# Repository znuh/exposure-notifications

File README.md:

# Exposure Notifications
Printed Circuit Boards for the Covid-19 Exposure Notifications Visualizer - 
[see this for more details](https://znu.nz/exposure_notifications-en)

To remake Exposure Notifications you need to get/make four things:
- a BBC micro:bit or Calliope Mini with the [microbit-corona-scanner](https://github.com/znuh/microbit-corona-scanner) installed
- a black 23x23cm RIBBA frame from IKEA
- the printed circuit board for the LEDs - see the leds/ directory of this repository
- the printed circuit board for the LED matrix controller - **either** matrixctl-v1 **OR** matrixctl-v2
  - matrixctl-v2 includes a socket for the micro:bit and a switching voltage regulator
  - matrixctl-v1 comes without a socket for the micro:bit and has no switching voltage regulator
  - v2 is more efficient and keeps the LED matrix driver cooler when more LEDs light up - therefore I recommend using v2

The printed circuit board designs are made with a **Nightly Development Build** of [KiCAD](https://kicad-pcb.org/).
If you want to open/edit them you also need a recent Nightly Development Build. If you just want to use the PCBs unmodified you can also use the gerber-files from the gerber-subdirectories.

## LED matrix board
The LED matrix board uses Würth 150141RV73100 LEDs. These are bicolor-LEDs but only the red LED is used.
The landing pads for the LEDs have been reduced to a minimum to hide the pads underneath the LEDs. All PCB tracks are on the back side of the PCB. 1206 0-Ohms resistors are used instead of vias to cross tracks.

## matrixctl v2 board ##
The part number of the micro:bit socket is PIS-1240. The Micro-USB connector is a Molex 105017-0001. You can get these parts and all additional components from digi-key.

Following a recommendation from the IS31FL3738 datasheet the board includes a Tantalum Capacitor to avoid audible noise produced by ceramics capacitors through the [piezoelectric effect](https://product.tdk.com/en/contact/faq/31_singing_capacitors_piezoelectric_effect.pdf). Tantalum is a conflict resource. I've chosen a Kemet T495B336K010ATE450 because Kemet is a sane choice in general and their handling of the issue sounds ok.

If you do not want to use the micro:bit socket you can also connect the micro:bit or a Calliope Mini to the pin header of the PCB. You need to connect I²C (SCL and SDA), 3V and GND.

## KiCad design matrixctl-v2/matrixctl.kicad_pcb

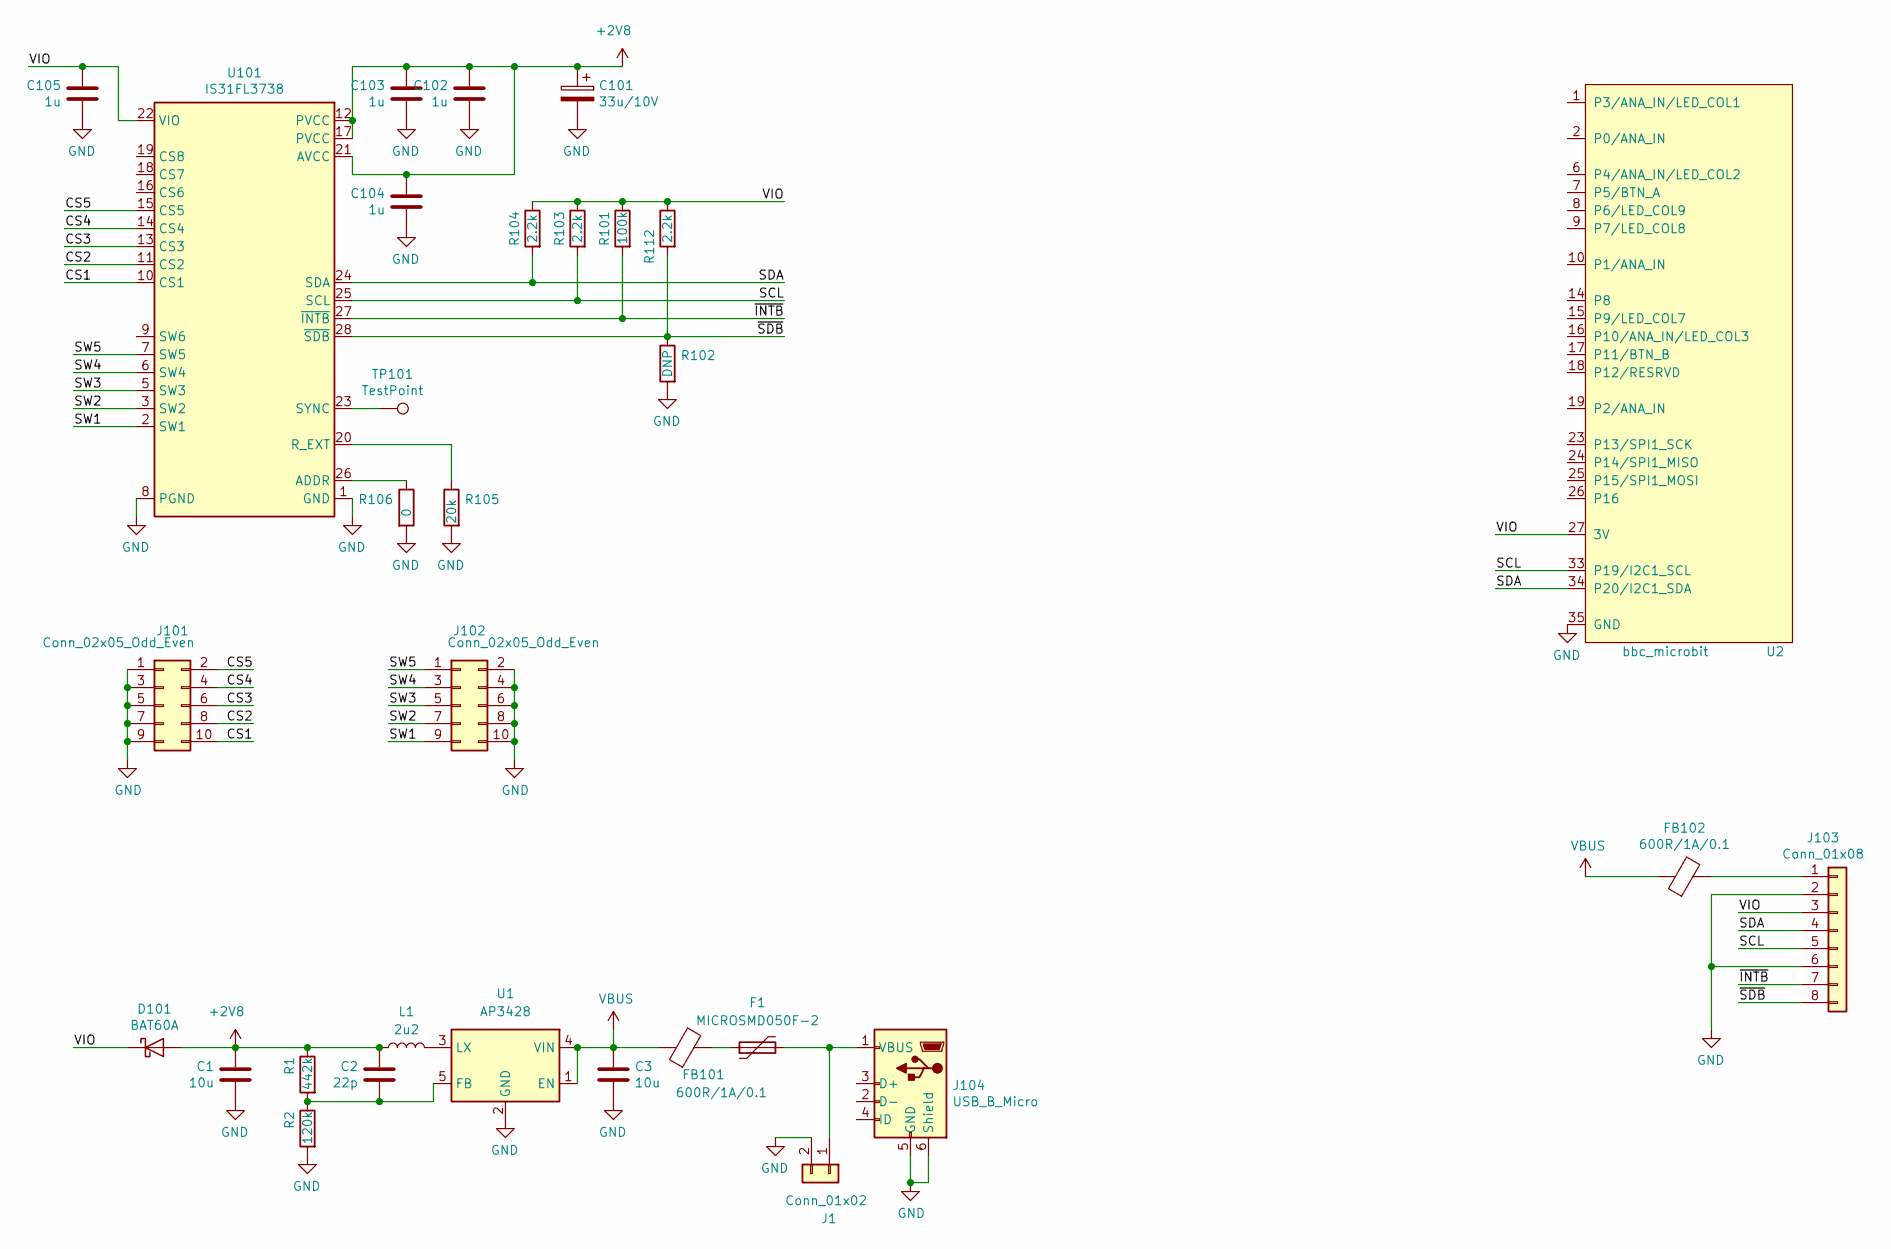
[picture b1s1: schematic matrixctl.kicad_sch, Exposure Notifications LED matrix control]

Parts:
C1, C3: 10u; C_0805_2012Metric
C2: 22p; C_0603_1608Metric
C101: 33u/10V; CP_EIA-3528-21_Kemet-B
C102, C103, C104, C105: 1u; C_0603_1608Metric
D101: BAT60A; D_SOD-323
F1: MICROSMD050F-2; Fuse_1210_3225Metric
FB101, FB102: 600R/1A/0.1; L_0805_2012Metric
J1: Conn_01x02; PinHeader_1x02_P2.54mm_Vertical
J101, J102: Conn_02x05_Odd_Even; PinSocket_2x05_P2.54mm_Vertical
J103: Conn_01x08; PinHeader_1x08_P2.54mm_Vertical
J104: USB_B_Micro; USB_Micro-B_Molex-105017-0001
L1: 2u2; L_1008_2520Metric
R1: 442k; R_0603_1608Metric
R2: 120k; R_0603_1608Metric
R101: 100k; R_0603_1608Metric
R102: DNP; R_0603_1608Metric
R103, R104, R112: 2.2k; R_0603_1608Metric
R105: 20k; R_0603_1608Metric
R106: 0; R_0603_1608Metric
TP101: TestPoint; TestPoint_Pad_D1.0mm
U1: AP3428; TSOT-23-5
U2: bbc_microbit; PIS-1240
U101: IS31FL3738; QFN-28-1EP_5x5mm_P0.5mm_EP3.5x3.5mm_ThermalVias

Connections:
+2V8: C1.1, C2.1, C101.1, C102.1, C103.1, C104.1, D101.2 (A), L1.2, R1.1, U101.12 (PVCC), U101.17 (PVCC), U101.21 (AVCC)
/CS1: J101.10, U101.10 (CS1)
/CS2: J101.8, U101.11 (CS2)
/CS3: J101.6, U101.13 (CS3)
/CS4: J101.4, U101.14 (CS4)
/CS5: J101.2, U101.15 (CS5)
/SCL: J103.5, R103.2, U2.33 (P19/I2C1_SCL), U101.25 (SCL)
/SDA: J103.4, R104.2, U2.34 (P20/I2C1_SDA), U101.24 (SDA)
/SW1: J102.9, U101.2 (SW1)
/SW2: J102.7, U101.3 (SW2)
/SW3: J102.5, U101.5 (SW3)
/SW4: J102.3, U101.6 (SW4)
/SW5: J102.1, U101.7 (SW5)
/VIO: C105.1, D101.1 (K), J103.3, R101.1, R103.1, R104.1, R112.1, U2.27 (3V), U2.28 (3V), U2.29 (3V), U2.30 (3V), U2.31 (3V), U2.32 (3V), U101.22 (VIO)
/~INTB: J103.7, R101.2, U101.27 (~INTB)
/~SDB: J103.8, R102.1, R112.2, U101.28 (~SDB)
GND: C1.2, C3.2, C101.2, C102.2, C103.2, C104.2, C105.2, J1.2, J101.1, J101.3, J101.5, J101.7, J101.9, J102.2, J102.4, J102.6, J102.8, J102.10, J103.2, J103.6, J104.5 (GND), J104.6 (Shield), R2.2, R102.2, R105.2, R106.2, U1.2 (GND), U2.35 (GND), U2.36 (GND), U2.37 (GND), U2.38 (GND), U2.39 (GND), U2.40 (GND), U101.1 (GND), U101.4 (PGND), U101.8 (PGND), U101.29 (PGND)
unnamed: C2.2, R1.2, R2.1, U1.5 (FB)
unnamed: F1.1, FB101.2
unnamed: F1.2, J1.1, J104.1 (VBUS)
unnamed: FB102.2, J103.1
unnamed: L1.1, U1.3 (LX)
unnamed: R105.1, U101.20 (R_EXT)
unnamed: R106.1, U101.26 (ADDR)
unnamed: TP101.1, U101.23 (SYNC)
unnamed: U2.2 (P0/ANA_IN), U2.3 (P0/ANA_IN), U2.4 (P0/ANA_IN), U2.5 (P0/ANA_IN)
unnamed: U2.10 (P1/ANA_IN), U2.11 (P1/ANA_IN), U2.12 (P1/ANA_IN), U2.13 (P1/ANA_IN)
unnamed: U2.19 (P2/ANA_IN), U2.20 (P2/ANA_IN), U2.21 (P2/ANA_IN), U2.22 (P2/ANA_IN)
VBUS: C3.1, FB101.1, FB102.1, U1.1 (EN), U1.4 (VIN)

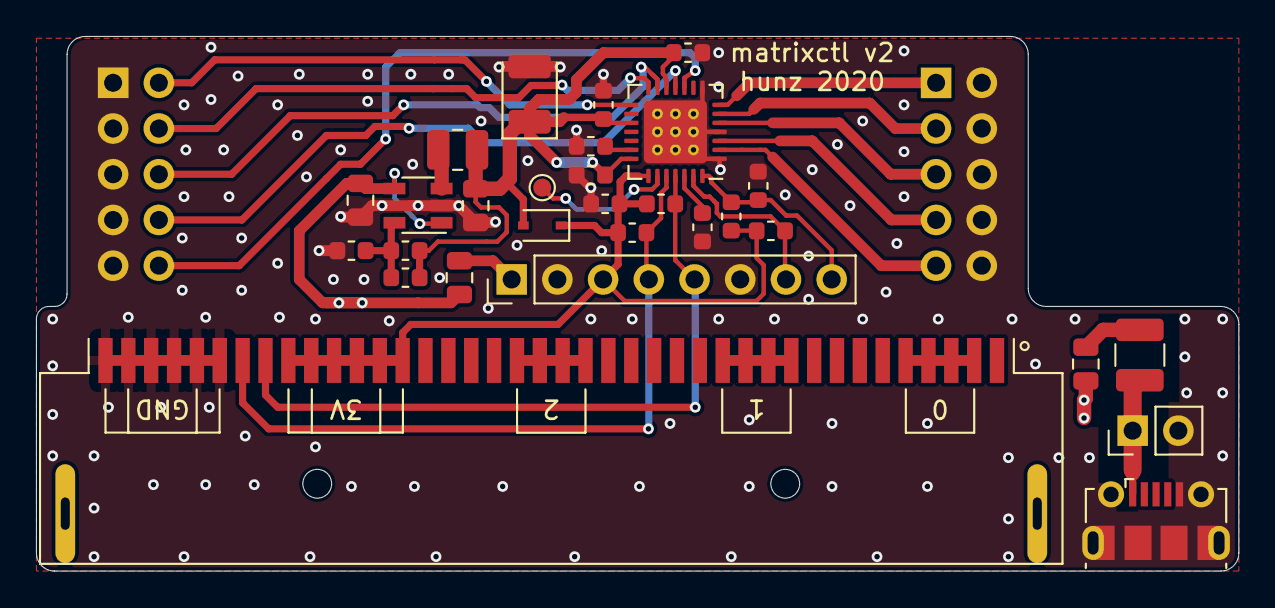
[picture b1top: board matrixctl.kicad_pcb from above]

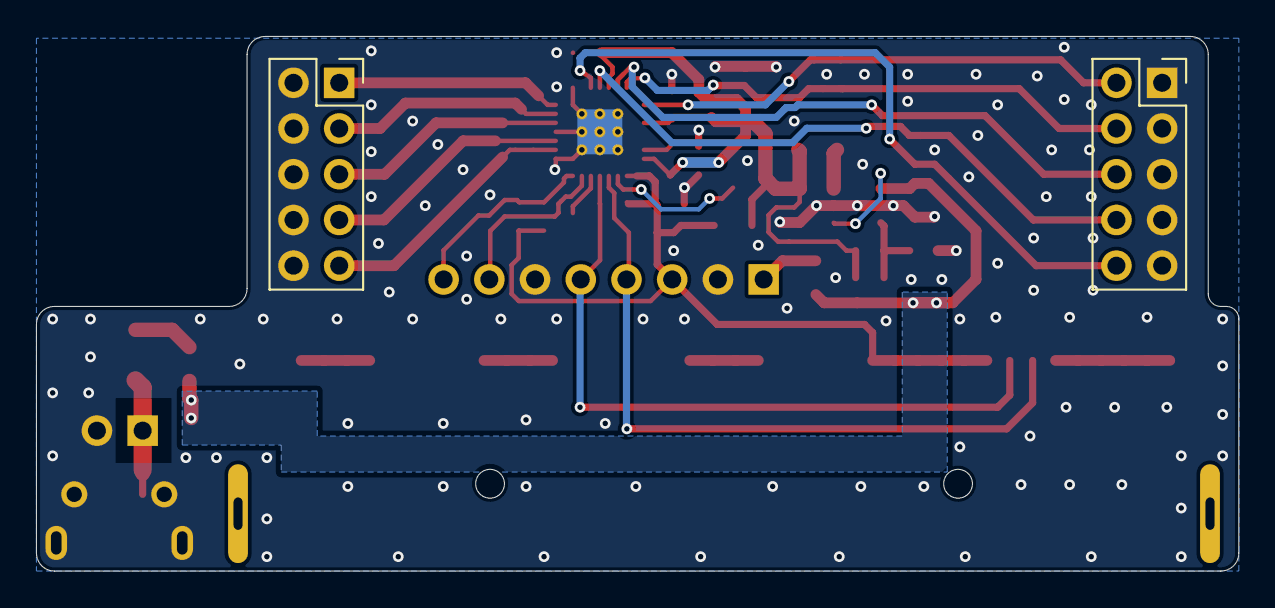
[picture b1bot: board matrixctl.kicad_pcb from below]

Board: 2 copper layers, 66.8 x 29.7 mm, 31 parts (2 on the bottom side), 29 nets.

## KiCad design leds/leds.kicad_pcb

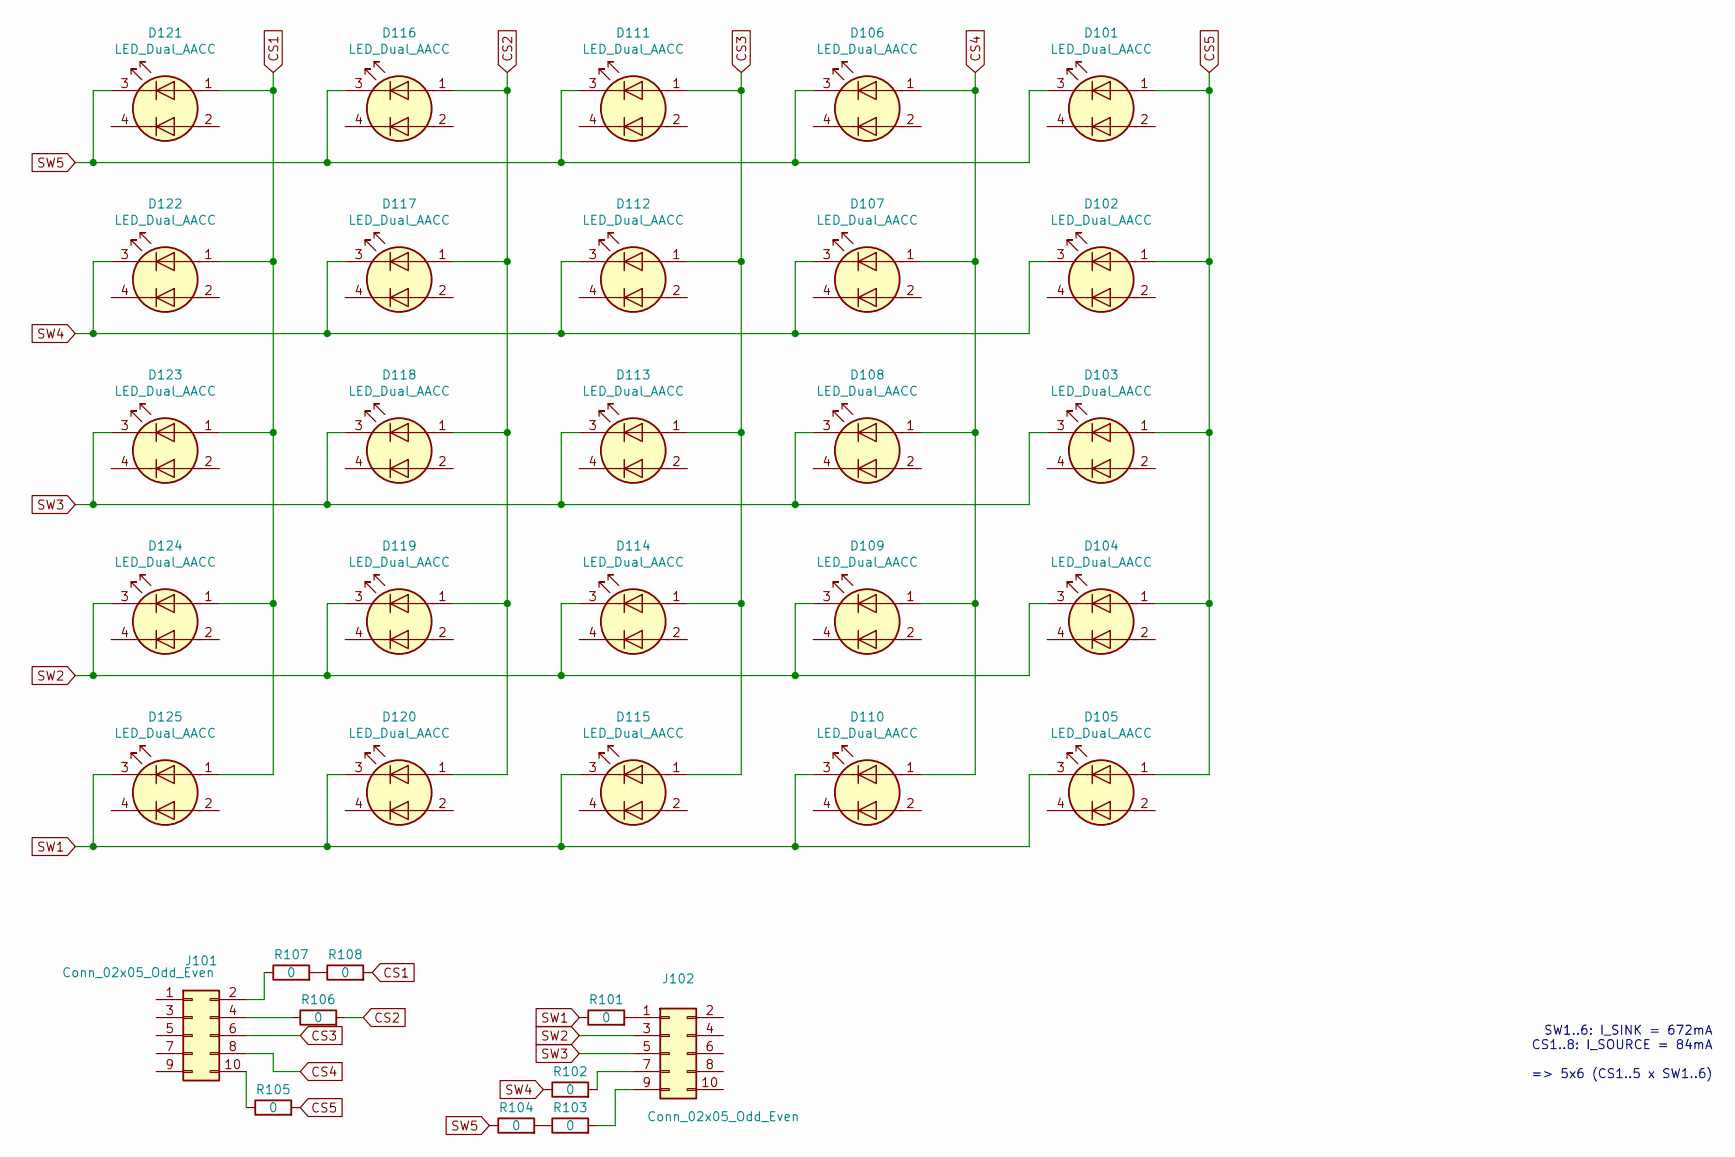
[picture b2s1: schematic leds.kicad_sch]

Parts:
D101, D102, D103, D104, D105, D106, D107, D108, D109, D110, D111, D112, D113, D114, D115, D116, D117, D118, D119, D120, D121, D122, D123, D124, D125: LED_Dual_AACC; Wuerth_150141RV73100
J101, J102: Conn_02x05_Odd_Even; PinHeader_2x05_P2.54mm_Vertical_SMD
R101, R102, R103, R104, R105, R106, R107, R108: 0; R_1206_3216Metric

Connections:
CS1: D121.1 (A1), D122.1 (A1), D123.1 (A1), D124.1 (A1), D125.1 (A1), R108.2
CS2: D116.1 (A1), D117.1 (A1), D118.1 (A1), D119.1 (A1), D120.1 (A1), R106.2
CS3: D111.1 (A1), D112.1 (A1), D113.1 (A1), D114.1 (A1), D115.1 (A1), J101.6
CS4: D106.1 (A1), D107.1 (A1), D108.1 (A1), D109.1 (A1), D110.1 (A1), J101.8
CS5: D101.1 (A1), D102.1 (A1), D103.1 (A1), D104.1 (A1), D105.1 (A1), R105.2
unnamed: J101.2, R107.1
unnamed: J101.4, R106.1
unnamed: J101.10, R105.1
unnamed: J102.1, R101.2
unnamed: J102.7, R102.2
unnamed: J102.9, R103.2
unnamed: R103.1, R104.2
unnamed: R107.2, R108.1
SW1: D105.3 (K1), D110.3 (K1), D115.3 (K1), D120.3 (K1), D125.3 (K1), R101.1
SW2: D104.3 (K1), D109.3 (K1), D114.3 (K1), D119.3 (K1), D124.3 (K1), J102.3
SW3: D103.3 (K1), D108.3 (K1), D113.3 (K1), D118.3 (K1), D123.3 (K1), J102.5
SW4: D102.3 (K1), D107.3 (K1), D112.3 (K1), D117.3 (K1), D122.3 (K1), R102.1
SW5: D101.3 (K1), D106.3 (K1), D111.3 (K1), D116.3 (K1), D121.3 (K1), R104.1

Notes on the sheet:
SW1..6: I_SINK = 672mA CS1..8: I_SOURCE = 84mA => 5x6 (CS1..5 x SW1..6)

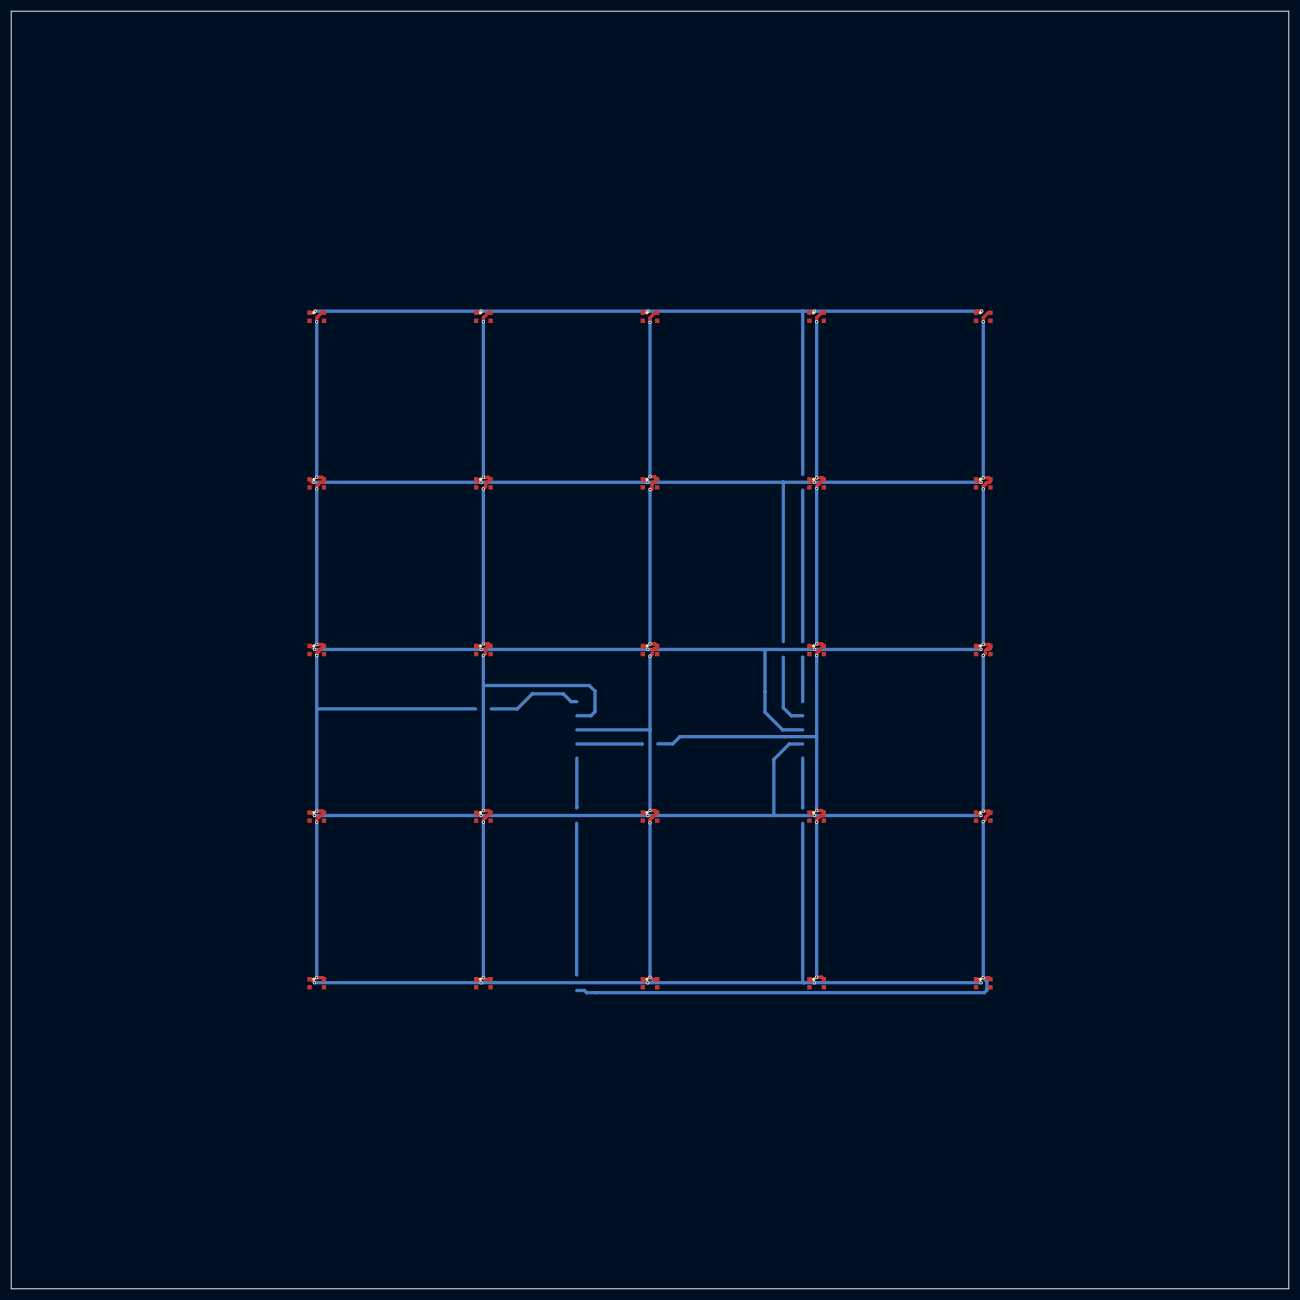
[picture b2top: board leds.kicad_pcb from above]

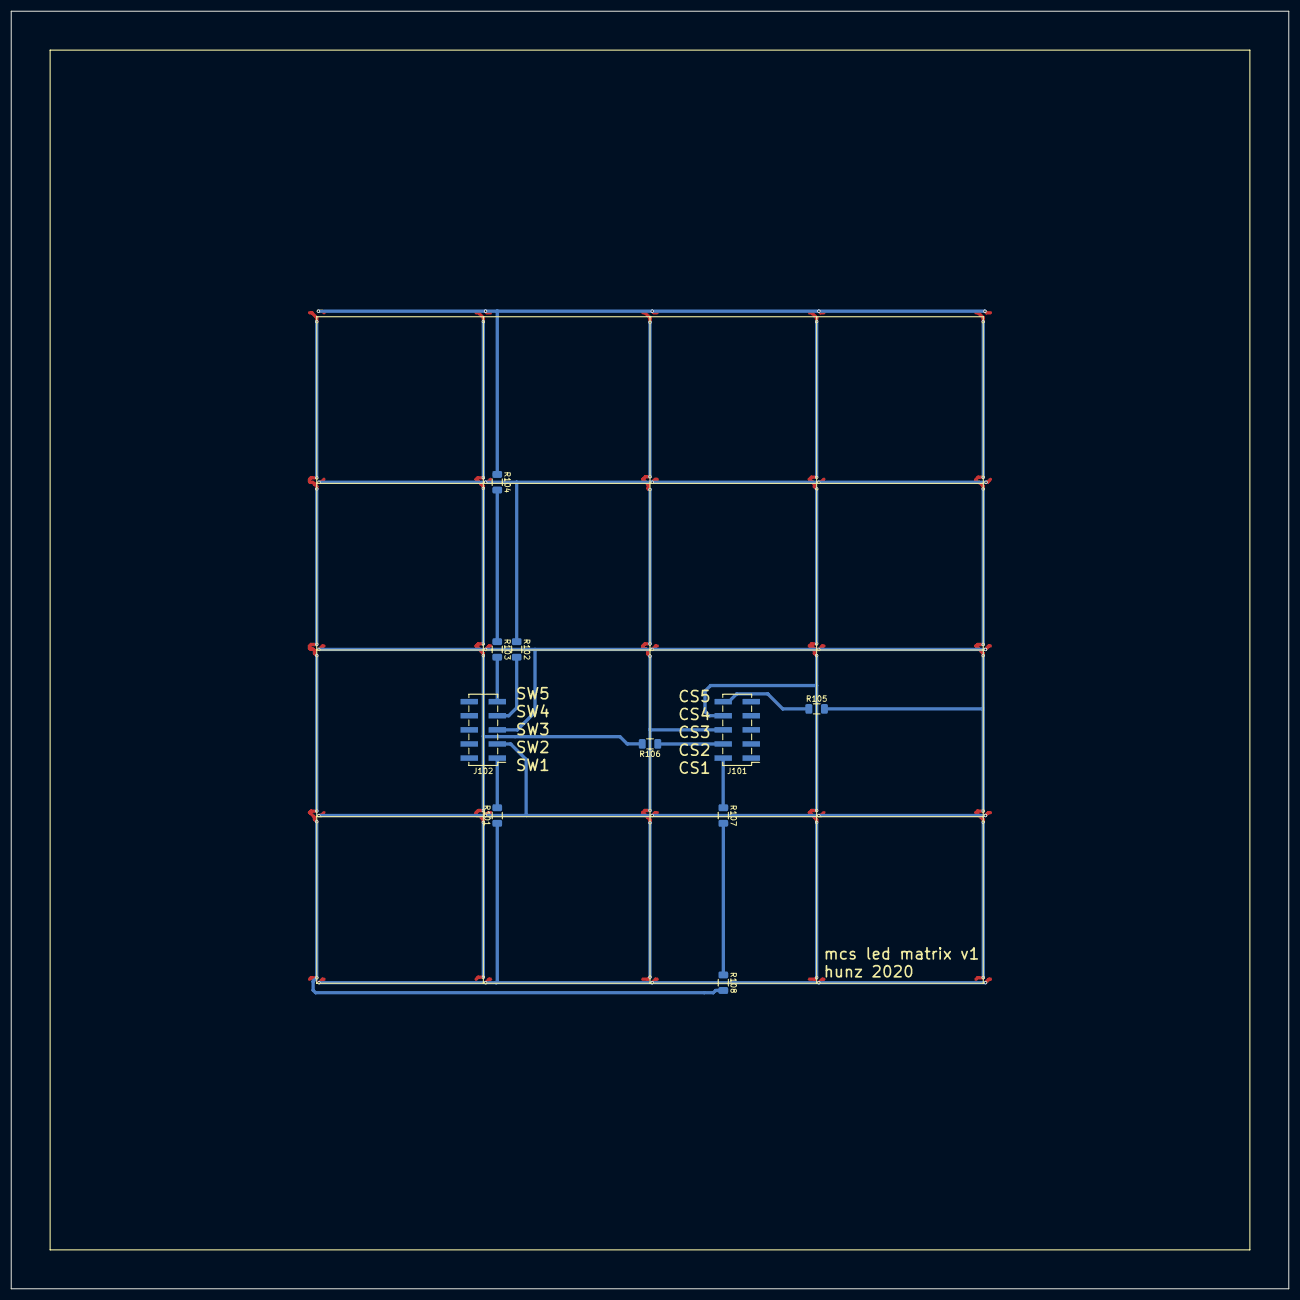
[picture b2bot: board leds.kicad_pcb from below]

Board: 2 copper layers, 230.0 x 230.0 mm, 35 parts (10 on the bottom side), 18 nets.

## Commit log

2020-09-23 initial import of matrixctl v2
2020-09-23 add gerber files
2020-09-23 change gerber output path
2020-09-23 initial import of LED matrix
2020-09-23 add lib table
2020-09-23 change gerber path
2020-09-23 remove unused LEDs, add paste in gerber output
2020-09-23 add gerber and libs
2020-09-23 actually it's v1
2020-09-23 update gerber
2020-09-23 add doc-fields in schematics, add PDFs of schematics
2020-09-23 C1 reduced from 22uF to 10uF to reduce risk of acoustic emmisions
2020-09-23 add renderings of PCBs
2020-09-23 22uF->33uF
2020-09-24 CERN OHL
